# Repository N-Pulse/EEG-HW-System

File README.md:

# EEG Hardware System

This repository contains the hardware design files for the N-Pulse EEG system.

The project is divided into three main subsystems:

- `eeg-board/` — EEG acquisition electronics
- `power-board/` — power supply, battery management, charging, and protection
- `headset/` — mechanical headset design and electrode integration

The electronic boards are designed in KiCad. Git is used for version control and collaboration between team members.

## Repository structure

```text
eeg-hw-system/
├── eeg-board/
├── power-board/
├── headset/
└── README.md

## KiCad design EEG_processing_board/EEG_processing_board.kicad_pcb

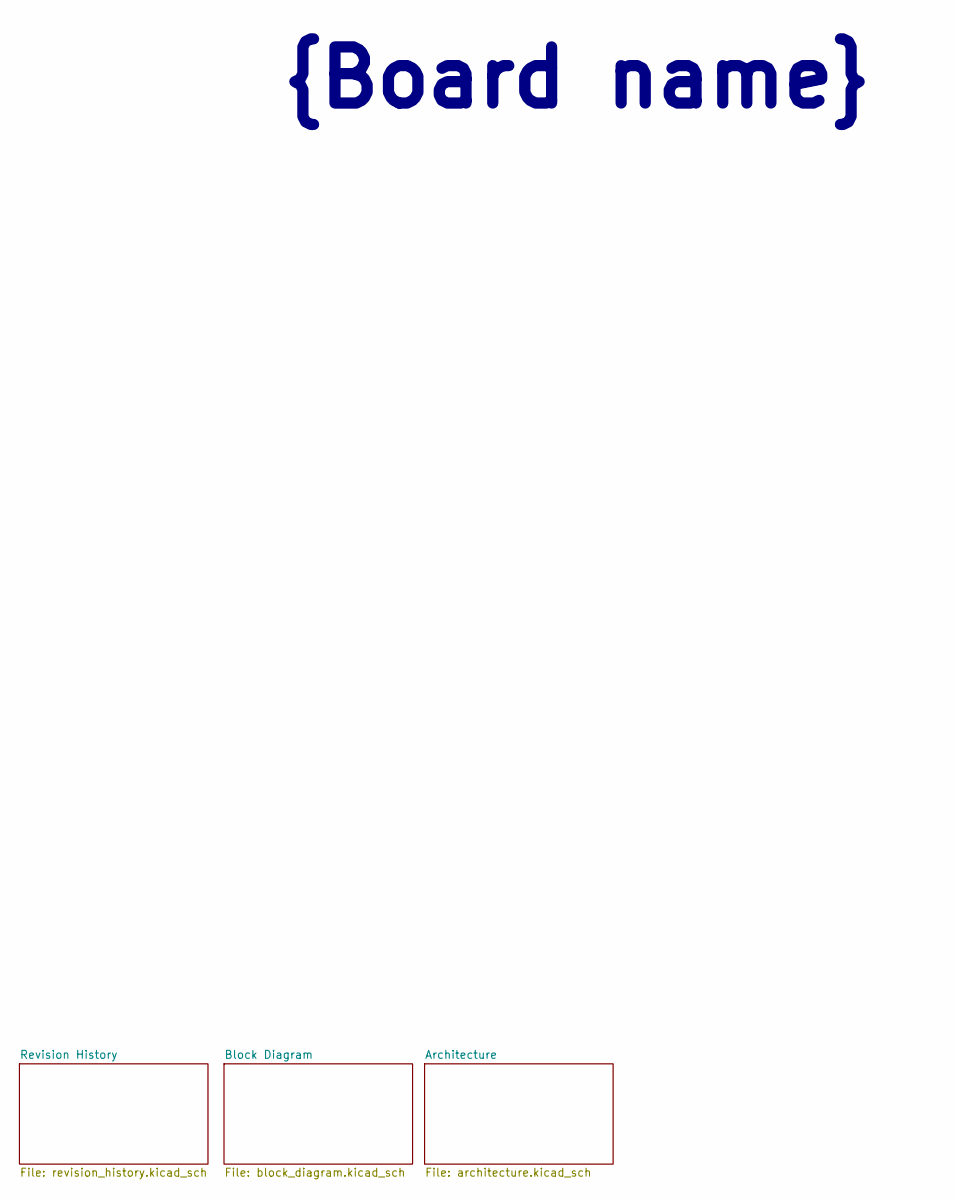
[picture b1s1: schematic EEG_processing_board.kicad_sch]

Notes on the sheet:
{Board name}

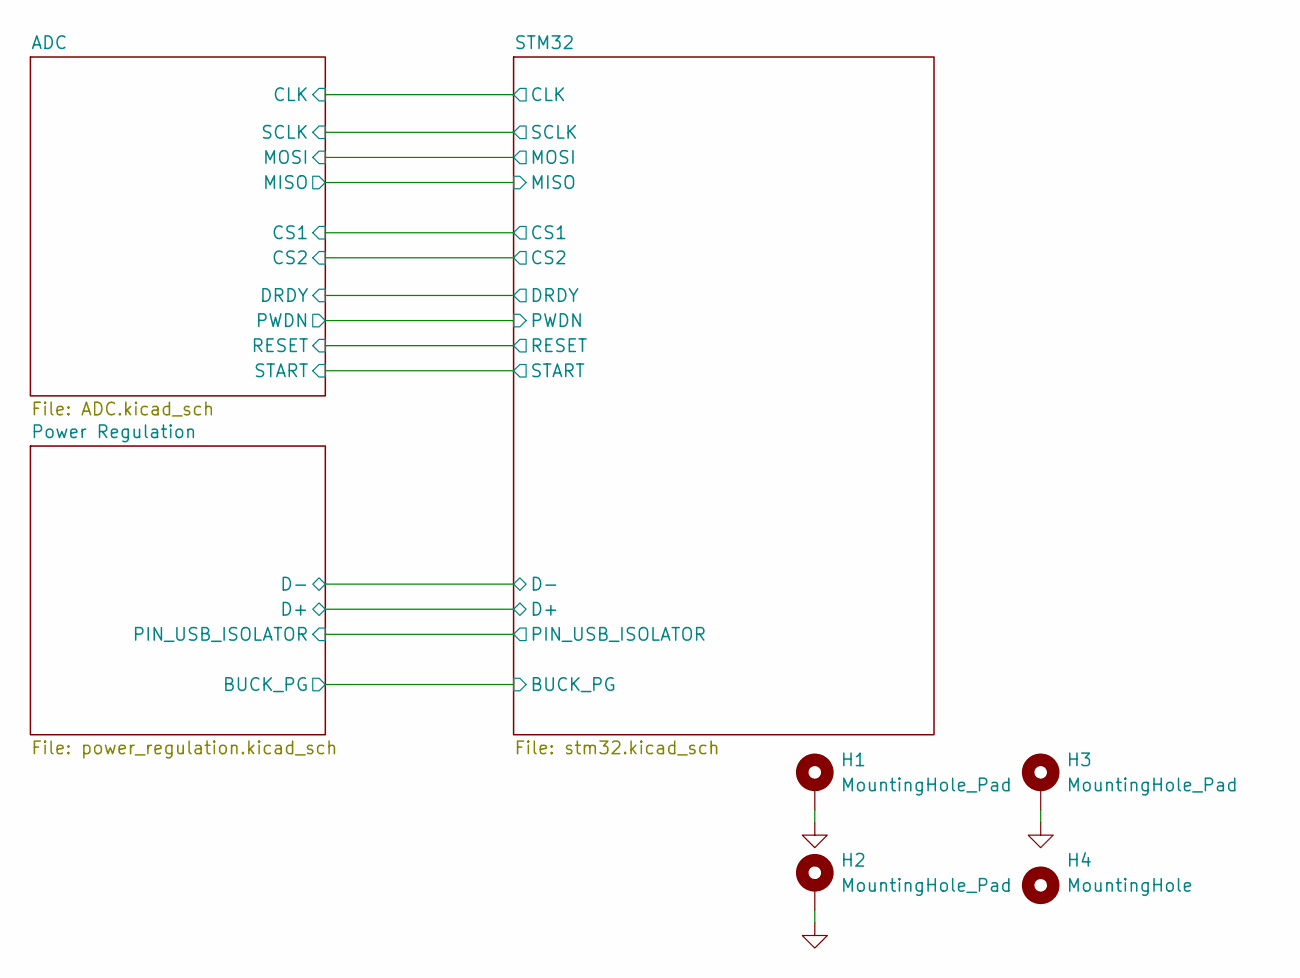
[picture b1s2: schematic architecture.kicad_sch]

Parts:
H1, H2, H3: MountingHole_Pad; MountingHole_3.2mm_M3_DIN965_Pad_TopBottom
H4: MountingHole; MountingHole_3.2mm_M3_DIN965

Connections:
GND: H1.1 (1_1), H2.1 (1_1), H3.1 (1_1); also elsewhere on the board

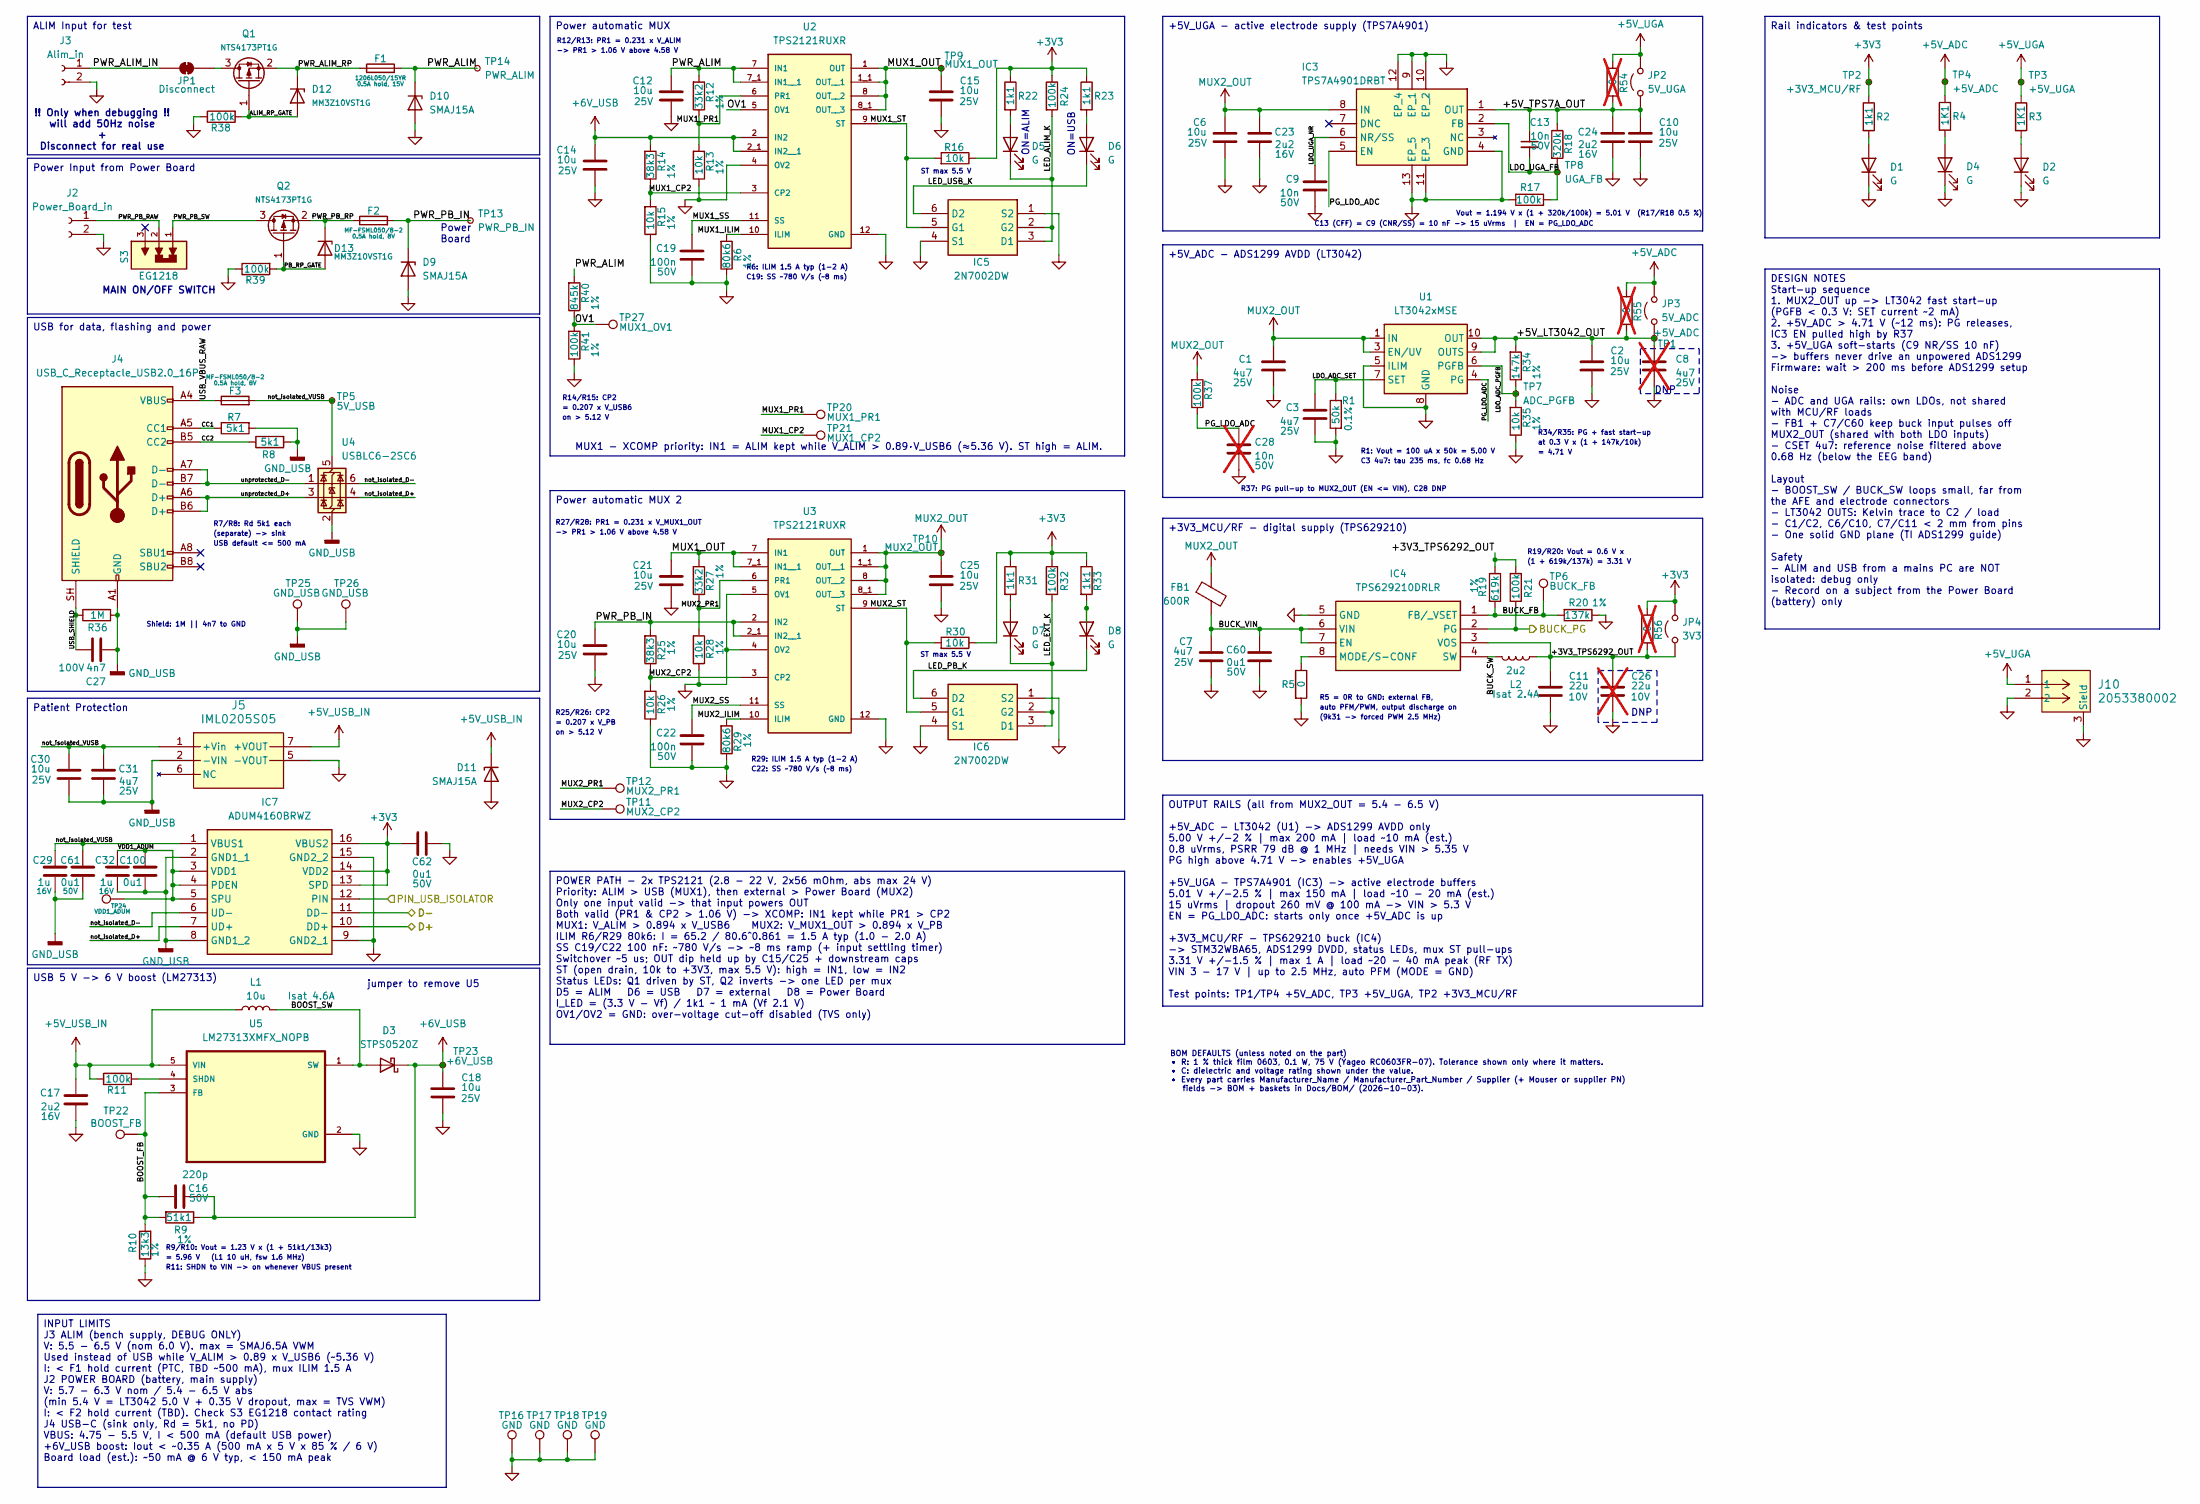
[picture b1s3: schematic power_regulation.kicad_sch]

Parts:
C1, C3, C7: 4u7; C_0603_1608Metric; Rating 25V; Tolerance 10%; Manufacturer_Part_Number GRM188R61E475KE11D
C2, C6, C10, C12, C14, C15, C18, C20, C21, C25, C30: 10u; C_0603_1608Metric; Rating 25V; Tolerance 20%; Manufacturer_Part_Number CC0603MRX5R8BB106
C8: 4u7; C_0603_1608Metric; Rating 25V; Tolerance 10%; Manufacturer_Part_Number GRM188R61E475KE11D; not fitted
C9, C13: 10n; C_0603_1608Metric; Rating 50V; Tolerance 5%; Manufacturer_Part_Number GRM1885C1H103JA01D
C11: 22u; C_0603_1608Metric; Rating 10V; Tolerance 20%; Manufacturer_Part_Number CC0603MPX5R6BB226
C16: 220p; C_0603_1608Metric; Rating 50V; Tolerance 5%; Manufacturer_Part_Number C0603C221J5GACTU
C17: 2u2; C_0603_1608Metric; Rating 16V; Tolerance 10%; Manufacturer_Part_Number EMK107BB7225KA-T
C19, C22: 100n; C_0603_1608Metric; Rating 50V; Tolerance 10%; Manufacturer_Part_Number C0603C104K5RACTU
C23, C24: 2u2; C_0603_1608Metric; Tolerance 10%; Rating 16V; Manufacturer_Part_Number EMK107BB7225KA-T
C26: 22u; C_0603_1608Metric; Rating 10V; Tolerance 20%; Manufacturer_Part_Number CC0603MPX5R6BB226; not fitted
C27: 4n7; C_0603_1608Metric; Rating 100V; Tolerance 10%; Manufacturer_Part_Number C0603C472K1RACTU
C28: 10n; C_0603_1608Metric; Rating 50V; Tolerance 5%; Manufacturer_Part_Number GRM1885C1H103JA01D; not fitted
C29, C32: 1u; C_0603_1608Metric; Tolerance 10%; Rating 16V; Manufacturer_Part_Number C0603C105K4RACTU
C31: 4u7; C_0603_1608Metric; Tolerance 10%; Rating 25V; Manufacturer_Part_Number GRM188R61E475KE11D
C60, C61, C62, C100: 0u1; C_0805_2012Metric; Tolerance 10%; Rating 50V; Manufacturer_Part_Number C0805C104K5RACTU
D1, D2, D4, D5, D6, D7, D8: G; LED_0603_1608Metric; Rating Green 571nm, Vf 2.0V; Manufacturer_Part_Number LTST-C191KGKT
D3: STPS0520Z; D_SOD-123; Rating 20V 0.5A Schottky; Manufacturer_Part_Number STPS0520Z
D9, D10, D11: SMAJ15A; D_SMA; Rating Vwm 15V, Vc 24.4V, 400W; Manufacturer_Part_Number SMAJ15A
D12, D13: MM3Z10VST1G; D_SOD-323F; Rating 10V 300mW zener; Manufacturer_Part_Number MM3Z10VST1G
F1: 1206L050/15YR; Fuse_1206_3216Metric; Rating 0.5A hold, 15V; Manufacturer_Part_Number 576-1206L050/15YR
F2, F3: MF-FSML050/8-2; Fuse_0603_1608Metric; Rating 0.5A hold, 8V; Manufacturer_Part_Number MF-FSML050/8-2
FB1: 600R; L_0603_1608Metric; Rating 600R@100MHz 1.3A; Manufacturer_Part_Number BLM18KG601SN1D
IC3: TPS7A4901DRBT; Mouser Part Number 595-TPS7A4901DRBT
IC4: TPS629210DRLR; SOTFL50P160X60-8N; Mouser Part Number 595-TPS629210DRLR
IC5, IC6: 2N7002DW; SOT65P210X110-6N; Mouser Part Number 512-2N7002DW
IC7: ADUM4160BRWZ; SOIC127P1032X265-16N; Mouser Part Number 584-ADUM4160BRWZ
J2: Power_Board_in; AMASS_XT30PW-M_1x02_P2.50mm_Horizontal; Manufacturer_Part_Number XT30PW-M
J3: Alim_in; PinHeader_1x02_P2.54mm_Vertical; Manufacturer_Part_Number 61300211121
J4: USB_C_Receptacle_USB2.0_16P; USB_C_Receptacle_GCT_USB4105-xx-A_16P_TopMnt_Horizontal; Manufacturer_Part_Number USB4110-GF-A
J5: IML0205S05; CONN5_05S05_XPP; Rating 2W 5V->5V, 4kV, 1xMOPP; Manufacturer_Part_Number IML0205S05
J10: 2053380002; CONN_2053380000-SD_02_MOL
JP1: Disconnect; SolderJumper-2_P1.3mm_Bridged_RoundedPad1.0x1.5mm
JP2: 5V_UGA; PinHeader_1x02_P2.54mm_Vertical_SMD_Pin1Left; Rating fit shunt Wurth 60900213421; Manufacturer_Part_Number 61300211121
JP3: 5V_ADC; PinHeader_1x02_P2.54mm_Vertical_SMD_Pin1Left; Rating fit shunt Wurth 60900213421; Manufacturer_Part_Number 61300211121
JP4: 3V3; PinHeader_1x02_P2.54mm_Vertical_SMD_Pin1Left; Rating fit shunt Wurth 60900213421; Manufacturer_Part_Number 61300211121
L1: 10u; L_Wuerth_MAPI-4030; Rating Isat 4.6A; Manufacturer_Part_Number 74438357100
L2: 2u2; L_Murata_DFE201610P; Rating Isat 2.4A; Manufacturer_Part_Number DFE201610E-2R2M=P2
Q1, Q2: NTS4173PT1G; SOT-323_SC-70; Rating P-ch -30V -1A, SC-70; Manufacturer_Part_Number NTS4173PT1G; Mouser Part Number 863-NTS4173PT1G
R1: 50k; R_0603_1608Metric; Tolerance 0.1%; Rating 0.15W; Manufacturer_Part_Number PNM0603E5002BST5
R2, R22, R23, R31, R33: 1k1; R_0603_1608Metric; Tolerance 1%; Rating 0.1W; Manufacturer_Part_Number RC0603FR-071K1L; Mouser Part Number 603-RC0603FR-071K1L
R3, R4: 1K1; R_0603_1608Metric; Tolerance 1%; Rating 0.1W; Manufacturer_Part_Number RC0603FR-071K1L; Mouser Part Number 603-RC0603FR-071K1L
R5: 0; R_0603_1608Metric; Rating 1A; Manufacturer_Part_Number RC0603JR-070RL; Mouser Part Number 603-RC0603JR-070RL
R6, R29: 80k6; R_0603_1608Metric; Tolerance 1%; Rating 0.1W; Manufacturer_Part_Number RC0603FR-0780K6L; Mouser Part Number 603-RC0603FR-0780K6L
R7, R8: 5k1; R_0603_1608Metric; Tolerance 1%; Rating 0.1W; Manufacturer_Part_Number RC0603FR-075K1L; Mouser Part Number 603-RC0603FR-075K1L
R9: 51k1; R_0603_1608Metric; Tolerance 1%; Rating 0.1W; Manufacturer_Part_Number RC0603FR-0751K1L; Mouser Part Number 603-RC0603FR-0751K1L
R10: 13k3; R_0603_1608Metric; Tolerance 1%; Rating 0.1W; Manufacturer_Part_Number RC0603FR-0713K3L; Mouser Part Number 603-RC0603FR-0713K3L
R11, R21, R24, R32, R37, R38, R39, R41: 100k; R_0603_1608Metric; Tolerance 1%; Rating 0.1W; Manufacturer_Part_Number RC0603FR-07100KL; Mouser Part Number 603-RC0603FR-07100KL
R12, R27: 33k2; R_0603_1608Metric; Tolerance 1%; Rating 0.1W; Manufacturer_Part_Number RC0603FR-0733K2L; Mouser Part Number 603-RC0603FR-0733K2L
R13, R15, R16, R26, R28, R30, R35: 10k; R_0603_1608Metric; Tolerance 1%; Rating 0.1W; Manufacturer_Part_Number RC0603FR-0710KL; Mouser Part Number 603-RC0603FR-0710KL
R14, R25: 38k3; R_0603_1608Metric; Tolerance 1%; Rating 0.1W; Manufacturer_Part_Number RC0603FR-0738K3L; Mouser Part Number 603-RC0603FR-0738K3L
R17: 100k; R_0603_1608Metric; Tolerance 0.5%; Rating 0.1W; Manufacturer_Part_Number RT0603DRD07100KL
R18: 320k; R_0603_1608Metric; Tolerance 0.5%; Rating 0.1W; Manufacturer_Part_Number RT0603DRD07320KL
R19: 619k; R_0603_1608Metric; Tolerance 1%; Rating 0.1W; Manufacturer_Part_Number RC0603FR-07619KL; Mouser Part Number 603-RC0603FR-07619KL
R20: 137k; R_0603_1608Metric; Tolerance 1%; Rating 0.1W; Manufacturer_Part_Number RC0603FR-07137KL; Mouser Part Number 603-RC0603FR-07137KL
R34: 147k; R_0603_1608Metric; Tolerance 1%; Rating 0.1W; Manufacturer_Part_Number RC0603FR-07147KL; Mouser Part Number 603-RC0603FR-07147KL
R36: 1M; R_0603_1608Metric; Tolerance 1%; Rating 0.1W; Manufacturer_Part_Number RC0603FR-071ML; Mouser Part Number 603-RC0603FR-071ML
R40: 845k; R_0603_1608Metric; Tolerance 1%; Rating 0.1W; Manufacturer_Part_Number RC0603FR-07845KL; Mouser Part Number 603-RC0603FR-07845KL
R54, R55, R56: 0; R_0603_1608Metric; Rating 1A; Manufacturer_Part_Number RC0603JR-070RL; Mouser Part Number 603-RC0603JR-070RL; not fitted
S3: EG1218; SW_EG1218; Rating 200mA 30V; Manufacturer_Part_Number EG1218
TP1, TP4: +5V_ADC; TestPoint_Pad_D1.5mm
TP2: +3V3_MCU/RF; TestPoint_Pad_D1.5mm
TP3: +5V_UGA; TestPoint_Pad_D1.5mm
TP5: 5V_USB; TestPoint_Pad_D1.5mm
TP6: BUCK_FB; TestPoint_Pad_D1.5mm
TP7: ADC_PGFB; TestPoint_Pad_D1.5mm
TP8: UGA_FB; TestPoint_Pad_D1.5mm
TP9: MUX1_OUT; TestPoint_Pad_D1.5mm
TP10: MUX2_OUT; TestPoint_Pad_D1.5mm
TP11: MUX2_CP2; TestPoint_Pad_D1.5mm
TP12: MUX2_PR1; TestPoint_Pad_D1.5mm
TP13: PWR_PB_IN; TestPoint_Pad_D1.5mm
TP14: PWR_ALIM; TestPoint_Pad_D1.5mm
TP16, TP17, TP18, TP19: GND; TestPoint_THTPad_D2.0mm_Drill1.0mm
TP20: MUX1_PR1; TestPoint_Pad_D1.5mm
TP21: MUX1_CP2; TestPoint_Pad_D1.5mm
TP22: BOOST_FB; TestPoint_Pad_D1.5mm
TP23: +6V_USB; TestPoint_Pad_D1.5mm
TP24: VDD1_ADUM; TestPoint_Pad_D1.5mm
TP25, TP26: GND_USB; TestPoint_THTPad_D2.0mm_Drill1.0mm
TP27: MUX1_OV1; TestPoint_Pad_D1.5mm
U1: LT3042xMSE; MSOP-10-1EP_3x3mm_P0.5mm_EP1.68x1.88mm; Manufacturer_Part_Number LT3042EMSE#PBF; Mouser Part Number 584-LT3042EMSE#PBF
U2, U3: TPS2121RUXR; IC_TPS2121RUXR; Manufacturer_Part_Number TPS2121RUXR; Mouser Part Number 595-TPS2121RUXR
U4: USBLC6-2SC6; SOT-23-6; Manufacturer_Part_Number USBLC6-2SC6
U5: LM27313XMFX_NOPB; SOT95P280X145-5N; Manufacturer_Part_Number LM27313XMF/NOPB

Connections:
+3V3: C62.2, IC7.13 (SPD), IC7.14 (VDD2), IC7.16 (VBUS2), JP4.2 (B), R2.1, R16.1, R22.1, R23.1, R24.1, R30.1, R31.1, R32.1, R33.1, R56.1, TP2.1 (1_1); also elsewhere on the board
+5V_ADC: JP3.2 (B), R4.1, R55.1, TP4.1 (1_1); also elsewhere on the board
+5V_UGA: J10.1, JP2.2 (B), R3.1, R54.1, TP3.1 (1_1)
+5V_USB_IN: C17.1, D11.1 (K), J5.7 (+VOUT), L1.1, R11.1, U5.5 (VIN)
+6V_USB: C14.1, C16.2, C18.1, D3.1 (K), R9.1, R14.2, TP23.1 (1_1), U2.2 (IN2), U2.2_1 (IN2__1)
/Architecture/Power Regulation/+3V3_TPS6292_OUT: C11.1, C26.1, IC4.3 (VOS), JP4.1 (A), L2.2, R19.1, R21.2, R56.2
/Architecture/Power Regulation/+5V_LT3042_OUT: C2.1, C8.1, JP3.1 (A), R34.2, R55.2, TP1.1 (1_1), U1.9 (OUTS), U1.10 (OUT)
/Architecture/Power Regulation/+5V_TPS7A_OUT: C10.1, C13.1, C24.1, IC3.1 (OUT), JP2.1 (A), R18.1, R54.2
/Architecture/Power Regulation/ALIM_RP_GATE: D12.2 (A), Q1.1 (G), R38.2
/Architecture/Power Regulation/BOOST_FB: C16.1, R9.2, R10.2, TP22.1 (1_1), U5.3 (FB)
/Architecture/Power Regulation/BOOST_SW: D3.2 (A), L1.2, U5.1 (SW)
/Architecture/Power Regulation/BUCK_FB: IC4.1 (FB/_VSET), R19.2, R20.2, TP6.1 (1_1)
/Architecture/Power Regulation/BUCK_PG: IC4.2 (PG), R21.1; also elsewhere on the board
/Architecture/Power Regulation/BUCK_SW: IC4.4 (SW), L2.1
/Architecture/Power Regulation/BUCK_VIN: C7.1, C60.2, FB1.2, IC4.6 (VIN), IC4.7 (EN)
/Architecture/Power Regulation/CC1: J4.A5 (CC1), R7.1
/Architecture/Power Regulation/CC2: J4.B5 (CC2), R8.1
/Architecture/Power Regulation/D+: IC7.10 (DD+); also elsewhere on the board
/Architecture/Power Regulation/D-: IC7.11 (DD-); also elsewhere on the board
/Architecture/Power Regulation/LDO_ADC_PGFB: R34.1, R35.2, TP7.1 (1_1), U1.6 (PGFB)
/Architecture/Power Regulation/LDO_ADC_SET: C3.1, R1.1, U1.7 (SET)
/Architecture/Power Regulation/LDO_UGA_FB: C13.2, IC3.2 (FB), R17.1, R18.2, TP8.1 (1_1)
/Architecture/Power Regulation/LDO_UGA_NR: C9.1, IC3.6 (NR/SS)
/Architecture/Power Regulation/LED_ALIM_K: D5.1 (K), IC5.2 (G2), IC5.3 (D1), R24.2
/Architecture/Power Regulation/LED_EXT_K: D7.1 (K), IC6.2 (G2), IC6.3 (D1), R32.2
/Architecture/Power Regulation/LED_PB_K: D8.1 (K), IC6.6 (D2)
/Architecture/Power Regulation/LED_USB_K: D6.1 (K), IC5.6 (D2)
/Architecture/Power Regulation/MUX1_CP2: R14.1, R15.2, TP21.1 (1_1), U2.3 (CP2)
/Architecture/Power Regulation/MUX1_ILIM: R6.2, U2.10 (ILIM)
/Architecture/Power Regulation/MUX1_OUT: C15.1, C21.1, R27.2, TP9.1 (1_1), U2.1 (OUT), U2.1_1 (OUT__1), U2.8 (OUT__2), U2.8_1 (OUT__3), U3.7 (IN1), U3.7_1 (IN1__1)
/Architecture/Power Regulation/MUX1_PR1: R12.1, R13.2, TP20.1 (1_1), U2.6 (PR1)
/Architecture/Power Regulation/MUX1_SS: C19.1, U2.11 (SS)
/Architecture/Power Regulation/MUX1_ST: IC5.5 (G1), R16.2, U2.9 (ST)
/Architecture/Power Regulation/MUX2_CP2: R25.1, R26.2, TP11.1 (1_1), U3.3 (CP2)
/Architecture/Power Regulation/MUX2_ILIM: R29.2, U3.10 (ILIM)
/Architecture/Power Regulation/MUX2_PR1: R27.1, R28.2, TP12.1 (1_1), U3.6 (PR1)
/Architecture/Power Regulation/MUX2_SS: C22.1, U3.11 (SS)
/Architecture/Power Regulation/MUX2_ST: IC6.5 (G1), R30.2, U3.9 (ST)
/Architecture/Power Regulation/OV1: R40.1, R41.2, TP27.1 (1_1), U2.5 (OV1)
/Architecture/Power Regulation/PB_RP_GATE: D13.2 (A), Q2.1 (G), R39.2
/Architecture/Power Regulation/PG_LDO_ADC: C28.1, IC3.5 (EN), R37.1, U1.4 (PG)
/Architecture/Power Regulation/PIN_USB_ISOLATOR: IC7.12 (PIN); also elsewhere on the board
/Architecture/Power Regulation/PWR_ALIM: C12.1, D10.1 (K), F1.2, R12.2, R40.2, TP14.1 (1_1), U2.7 (IN1), U2.7_1 (IN1__1)
/Architecture/Power Regulation/PWR_ALIM_IN: J3.1, JP1.2 (B)
/Architecture/Power Regulation/PWR_ALIM_RP: D12.1 (K), F1.1, Q1.2 (S)
/Architecture/Power Regulation/PWR_PB_IN: C20.1, D9.1 (K), F2.2, R25.2, TP13.1 (1_1), U3.2 (IN2), U3.2_1 (IN2__1)
/Architecture/Power Regulation/PWR_PB_RAW: J2.1, S3.2
/Architecture/Power Regulation/PWR_PB_RP: D13.1 (K), F2.1, Q2.2 (S)
/Architecture/Power Regulation/PWR_PB_SW: Q2.3 (D), S3.1
/Architecture/Power Regulation/USB_SHIELD: C27.1, J4.SH (SHIELD), R36.1
/Architecture/Power Regulation/USB_VBUS_RAW: F3.1, J4.A4 (VBUS), J4.A9 (VBUS), J4.B4 (VBUS), J4.B9 (VBUS)
/Architecture/Power Regulation/VDD1_ADUM: C32.1, C100.2, IC7.3 (VDD1), IC7.4 (PDEN), IC7.5 (SPU), TP24.1 (1_1)
/Architecture/Power Regulation/not_isolated_D+: IC7.7 (UD+), U4.4 (I/O2)
/Architecture/Power Regulation/not_isolated_D-: IC7.6 (UD-), U4.6 (I/O1)
/Architecture/Power Regulation/not_isolated_VUSB: C29.1, C30.1, C31.1, C61.2, F3.2, IC7.1 (VBUS1), J5.1 (+Vin), TP5.1 (1_1), U4.5 (VBUS)
/Architecture/Power Regulation/unprotected_D+: J4.A6 (D+), J4.B6 (D+), U4.3 (I/O2)
/Architecture/Power Regulation/unprotected_D-: J4.A7 (D-), J4.B7 (D-), U4.1 (I/O1)
GND: C1.2, C2.2, C3.2, C6.2, C7.2, C8.2, C9.2, C10.2, C11.2, C12.2, C14.2, C15.2, C17.2, C18.2, C19.2, C20.2, C21.2, C22.2, C23.2, C24.2, C25.2, C26.2, C28.2, C60.1, C62.1, D1.1 (K), D2.1 (K), D4.1 (K), D9.2 (A), D10.2 (A), D11.2 (A), IC3.4 (GND), IC3.9 (EP_1), IC3.10 (EP_2), IC3.11 (EP_3), IC3.12 (EP_4), IC3.13 (EP_5), IC4.5 (GND), IC5.1 (S2), IC5.4 (S1), IC6.1 (S2), IC6.4 (S1), IC7.9 (GND2_1), IC7.15 (GND2_2), J2.2, J3.2, J5.5 (-VOUT), J10.2, J10.3 (Sield), J10.4 (Sield), R1.2, R5.2, R6.1, R10.1, R13.1, R15.1, R17.2, R20.1, R26.1, R28.1, R29.1, R35.1, R38.1, R39.1, R41.1, TP16.1 (1_1), TP17.1 (1_1), TP18.1 (1_1), TP19.1 (1_1), U1.5 (ILIM), U1.8 (GND), U1.11 (GND), U2.4 (OV2), U2.12 (GND), U3.4 (OV2), U3.5 (OV1), U3.12 (GND), U5.2 (GND); also elsewhere on the board
GND_USB: C27.2, C29.2, C30.2, C31.2, C32.2, C61.1, C100.1, IC7.2 (GND1_1), IC7.8 (GND1_2), J4.A1 (GND), J4.A12 (GND), J4.B1 (GND), J4.B12 (GND), J5.2 (-VIN), R7.2, R8.2, R36.2, TP25.1 (1_1), TP26.1 (1_1), U4.2 (GND)
MUX2_OUT: C1.1, C6.1, C23.1, C25.1, FB1.1, IC3.8 (IN), R37.2, TP10.1 (1_1), U1.1 (IN), U1.2 (IN), U1.3 (EN/UV), U3.1 (OUT), U3.1_1 (OUT__1), U3.8 (OUT__2), U3.8_1 (OUT__3)
unnamed: D1.2 (A), R2.2
unnamed: D2.2 (A), R3.2
unnamed: D4.2 (A), R4.2
unnamed: D5.2 (A), R22.2
unnamed: D6.2 (A), R23.2
unnamed: D7.2 (A), R31.2
unnamed: D8.2 (A), R33.2
unnamed: IC4.8 (MODE/S-CONF), R5.1
unnamed: JP1.1 (A), Q1.3 (D)
unnamed: R11.2, U5.4 (SHDN)

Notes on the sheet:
auto PFM/PWM, output discharge on
jumper to remove U5
C3 4u7: tau 235 ms, fc 0.68 Hz
= 5.96 V (L1 10 uH, fsw 1.6 MHz)
= 0.207 x V_USB6
R29: ILIM 1.5 A typ (1-2 A)
R6: ILIM 1.5 A typ (1-2 A)
-> PR1 > 1.06 V above 4.58 V
ON=ALIM
ST max 5.5 V
R12/R13: PR1 = 0.231 x V_ALIM
= 4.71 V
C19: SS ~780 V/s (~8 ms)
= 0.207 x V_PB
on > 5.12 V
R9/R10: Vout = 1.23 V x (1 + 51k1/13k3)
(1 + 619k/137k) = 3.31 V
(separate) -> sink
!! Only when debugging !! will add 50Hz noise + Disconnect for real use
MUX1 - XCOMP priority: IN1 = ALIM kept while V_ALIM > 0.89·V_USB6 (≈5.36 V). ST high = ALIM.
ON=USB
R19/R20: Vout = 0.6 V x
R7/R8: Rd 5k1 each
BOM DEFAULTS (unless noted on the part) • R: 1 % thick film 0603, 0.1 W, 75 V (Yageo RC0603FR-07). Tolerance shown only where it matters. • C: dielectric and voltage rating shown under the value. • Every part carries Manufacturer_Name / Manufacturer_Part_Number / Supplier (+ Mouser or supplier PN) 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
Vout = 1.194 V x (1 + 320k/100k) = 5.01 V (R17/R18 0.5 %)
USB default <= 500 mA
R37: PG pull-up to MUX2_OUT (EN <= VIN), C28 DNP
Shield: 1M || 4n7 to GND
R5 = 0R to GND: external FB,
R1: Vout = 100 uA x 50k = 5.00 V
at 0.3 V x (1 + 147k/10k)
DNP
R25/R26: CP2
MAIN ON/OFF SWITCH
R11: SHDN to VIN -> on whenever VBUS present
Power Board
C13 (CFF) = C9 (CNR/SS) = 10 nF -> 15 uVrms | EN = PG_LDO_ADC
R34/R35: PG + fast start-up
(9k31 -> forced PWM 2.5 MHz)
C22: SS ~780 V/s (~8 ms)

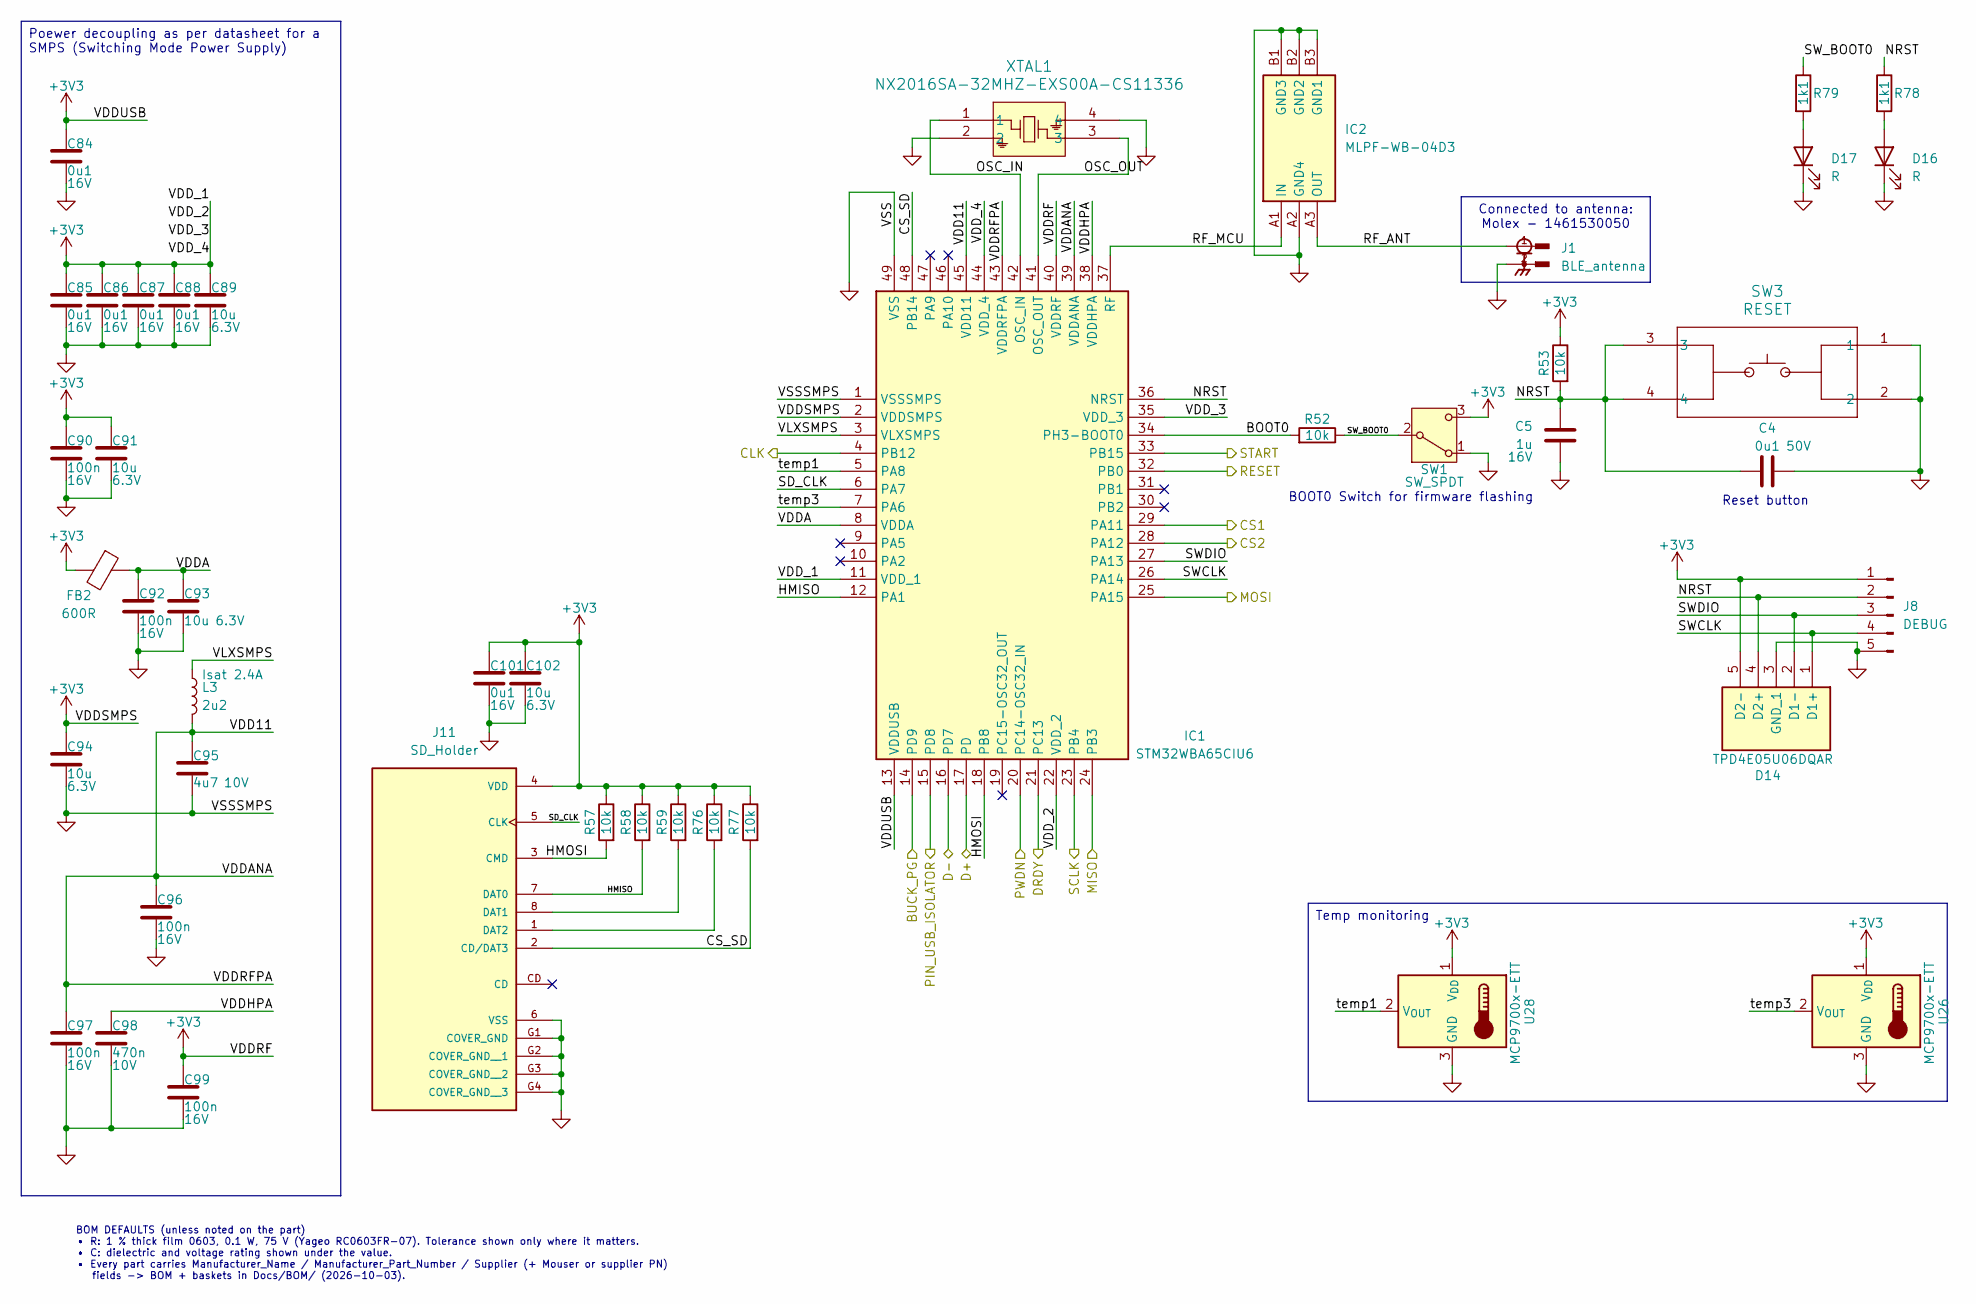
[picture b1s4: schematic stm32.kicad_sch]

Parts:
C4: 0u1; C_0603_1608Metric; Rating 50V; Tolerance 10%; Manufacturer_Part_Number C0603C104K5RACTU
C5: 1u; C_0603_1608Metric; Rating 16V; Tolerance 10%; Manufacturer_Part_Number C0603C105K4RACTU
C84, C85, C86, C87, C88, C101: 0u1; C_0402_1005Metric; Rating 16V; Tolerance 10%; Manufacturer_Part_Number CC0402KRX7R7BB104
C89, C91, C93, C94, C102: 10u; C_0402_1005Metric; Rating 6.3V; Tolerance 20%; Manufacturer_Part_Number GRM155R60J106ME15D
C90, C92, C96, C97, C99: 100n; C_0402_1005Metric; Rating 16V; Tolerance 10%; Manufacturer_Part_Number CC0402KRX7R7BB104
C95: 4u7; C_0402_1005Metric; Rating 10V; Tolerance 10%; Manufacturer_Part_Number C1005X5R1A475K050BC
C98: 470n; C_0402_1005Metric; Rating 10V; Tolerance 10%; Manufacturer_Part_Number GRM155R61A474KE15D
D14: TPD4E05U06DQAR; DQA_R-PUSON-N10_; Mouser Part Number 595-TPD4E05U06DQAR
D16, D17: R; LED_0603_1608Metric; Rating Green 571nm, Vf 2.0V; Manufacturer_Part_Number LTST-C191KGKT
FB2: 600R; L_0603_1608Metric; Rating 600R@100MHz 1.3A; Manufacturer_Part_Number BLM18KG601SN1D
IC1: STM32WBA65CIU6; QFN50P700X700X60-49N-D; Mouser Part Number 511-STM32WBA65CIU6
IC2: MLPF-WB-04D3; CSPG_2025; Mouser Part Number 511-MLPF-WB-04D3
J1: BLE_antenna; TE_CONMHF1-SMD-T; PARTREV 09/22
J8: DEBUG; PinHeader_1x05_P2.54mm_Vertical_SMD_Pin1Right; Manufacturer_Part_Number 61300511121
J11: SD_Holder; CUI_MSD-1-A; PARTREV 1.0
L3: 2u2; L_Murata_DFE201610P; Rating Isat 2.4A; Manufacturer_Part_Number DFE201610E-2R2M=P2
R52, R53, R57, R58, R59, R76, R77: 10k; R_0603_1608Metric; Tolerance 1%; Rating 0.1W; Manufacturer_Part_Number RC0603FR-0710KL; Mouser Part Number 603-RC0603FR-0710KL
R78, R79: 1k1; R_0603_1608Metric; Tolerance 1%; Rating 0.1W; Manufacturer_Part_Number RC0603FR-071K1L; Mouser Part Number 603-RC0603FR-071K1L
SW1: SW_SPDT; SW_SPDT_PCM12; Manufacturer_Part_Number PCM12SMTR
SW3: RESET; SW4_SKRPABE010_ALPS; Manufacturer_Part_Number SKRPABE010
U26, U28: MCP9700x-ETT; SOT-23; Manufacturer_Part_Number MCP9700AT-E/TT
XTAL1: NX2016SA-32MHZ-EXS00A-CS11336; NX2016SA_NDK; Rating 32MHz 8pF ±10ppm; Manufacturer_Part_Number NX2016SA-32MHZ-EXS00A-CS11336

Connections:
+3V3: C84.1, C85.1, C86.1, C87.1, C88.1, C89.1, C90.1, C91.1, C94.1, C99.1, C101.1, C102.1, D14.5 (D2-), D14.6 (NC_1), FB2.2, IC1.2 (VDDSMPS), IC1.11 (VDD_1), IC1.13 (VDDUSB), IC1.22 (VDD_2), IC1.35 (VDD_3), IC1.40 (VDDRF), IC1.44 (VDD_4), J8.1, J11.4 (VDD), R53.1, R57.1, R58.1, R59.1, R76.1, R77.1, SW1.3 (C), U26.1 (V_{DD}), U28.1 (V_{DD}); also elsewhere on the board
/Architecture/ADC/CLK: IC1.4 (PB12); also elsewhere on the board
/Architecture/ADC/CS1: IC1.29 (PA11); also elsewhere on the board
/Architecture/ADC/CS2: IC1.28 (PA12); also elsewhere on the board
/Architecture/ADC/DRDY: IC1.21 (PC13); also elsewhere on the board
/Architecture/ADC/MISO: IC1.24 (PB3); also elsewhere on the board
/Architecture/ADC/MOSI: IC1.25 (PA15); also elsewhere on the board
/Architecture/ADC/PWDN: IC1.20 (PC14-OSC32_IN); also elsewhere on the board
/Architecture/ADC/RESET: IC1.32 (PB0); also elsewhere on the board
/Architecture/ADC/SCLK: IC1.23 (PB4); also elsewhere on the board
/Architecture/ADC/START: IC1.33 (PB15); also elsewhere on the board
/Architecture/Power Regulation/BUCK_PG: IC1.14 (PD9); also elsewhere on the board
/Architecture/Power Regulation/D+: IC1.17 (PD); also elsewhere on the board
/Architecture/Power Regulation/D-: IC1.16 (PD7); also elsewhere on the board
/Architecture/Power Regulation/PIN_USB_ISOLATOR: IC1.15 (PD8); also elsewhere on the board
/Architecture/STM32/BOOT0: IC1.34 (PH3-BOOT0), R52.2
/Architecture/STM32/CS_SD: IC1.48 (PB14), J11.2 (CD/DAT3), R77.2
/Architecture/STM32/HMISO: IC1.12 (PA1), J11.7 (DAT0), R58.2
/Architecture/STM32/HMOSI: IC1.18 (PB8), J11.3 (CMD), R57.2
/Architecture/STM32/NRST: C4.1, C5.1, D14.4 (D2+), D14.7 (NC_2), IC1.36 (NRST), J8.2, R53.2, R78.1, SW3.3, SW3.4
/Architecture/STM32/OSC_IN: IC1.42 (OSC_IN), XTAL1.1
/Architecture/STM32/OSC_OUT: IC1.41 (OSC_OUT), XTAL1.3
/Architecture/STM32/RF_ANT: IC2.A3 (OUT), J1.1
/Architecture/STM32/RF_MCU: IC1.37 (RF), IC2.A1 (IN)
/Architecture/STM32/SD_CLK: IC1.6 (PA7), J11.5 (CLK)
/Architecture/STM32/SWCLK: D14.1 (D1+), D14.10 (NC_4), IC1.26 (PA14), J8.4
/Architecture/STM32/SWDIO: D14.2 (D1-), D14.9 (NC_3), IC1.27 (PA13), J8.3
/Architecture/STM32/SW_BOOT0: R52.1, R79.1, SW1.2 (B)
/Architecture/STM32/VDD11: C95.1, C96.1, C97.1, IC1.39 (VDDANA), IC1.43 (VDDRFPA), IC1.45 (VDD11), L3.2
/Architecture/STM32/VDDA: C92.1, C93.1, FB2.1, IC1.8 (VDDA)
/Architecture/STM32/VDDHPA: C98.1, IC1.38 (VDDHPA)
/Architecture/STM32/VLXSMPS: IC1.3 (VLXSMPS), L3.1
/Architecture/STM32/temp1: IC1.5 (PA8), U28.2 (V_{OUT})
/Architecture/STM32/temp3: IC1.7 (PA6), U26.2 (V_{OUT})
GND: C4.2, C5.2, C84.2, C85.2, C86.2, C87.2, C88.2, C89.2, C90.2, C91.2, C92.2, C93.2, C94.2, C95.2, C96.2, C97.2, C98.2, C99.2, C101.2, C102.2, D14.3 (GND_1), D14.8 (GND_2), D16.1 (K), D17.1 (K), IC1.1 (VSSSMPS), IC1.49 (VSS), IC2.A2 (GND4), IC2.B1 (GND3), IC2.B2 (GND2), IC2.B3 (GND1), J1.2, J1.3, J1.4, J8.5, J11.6 (VSS), J11.G1 (COVER_GND), J11.G2 (COVER_GND__1), J11.G3 (COVER_GND__2), J11.G4 (COVER_GND__3), SW1.1 (A), SW3.1, SW3.2, U26.3 (GND), U28.3 (GND), XTAL1.2, XTAL1.4; also elsewhere on the board
unnamed: D16.2 (A), R78.2
unnamed: D17.2 (A), R79.2
unnamed: J11.8 (DAT1), R59.2
unnamed: J11.1 (DAT2), R76.2

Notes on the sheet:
BOOT0 Switch for firmware flashing
Reset button
BOM DEFAULTS (unless noted on the part) • R: 1 % thick film 0603, 0.1 W, 75 V (Yageo RC0603FR-07). Tolerance shown only where it matters. • C: dielectric and voltage rating shown under the value. • Every part carries Manufacturer_Name / Manufacturer_Part_Number / Supplier (+ Mouser or supplier PN) 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
Temp monitoring
Connected to antenna: Molex - 1461530050
Poewer decoupling as per datasheet for a SMPS (Switching Mode Power Supply)
